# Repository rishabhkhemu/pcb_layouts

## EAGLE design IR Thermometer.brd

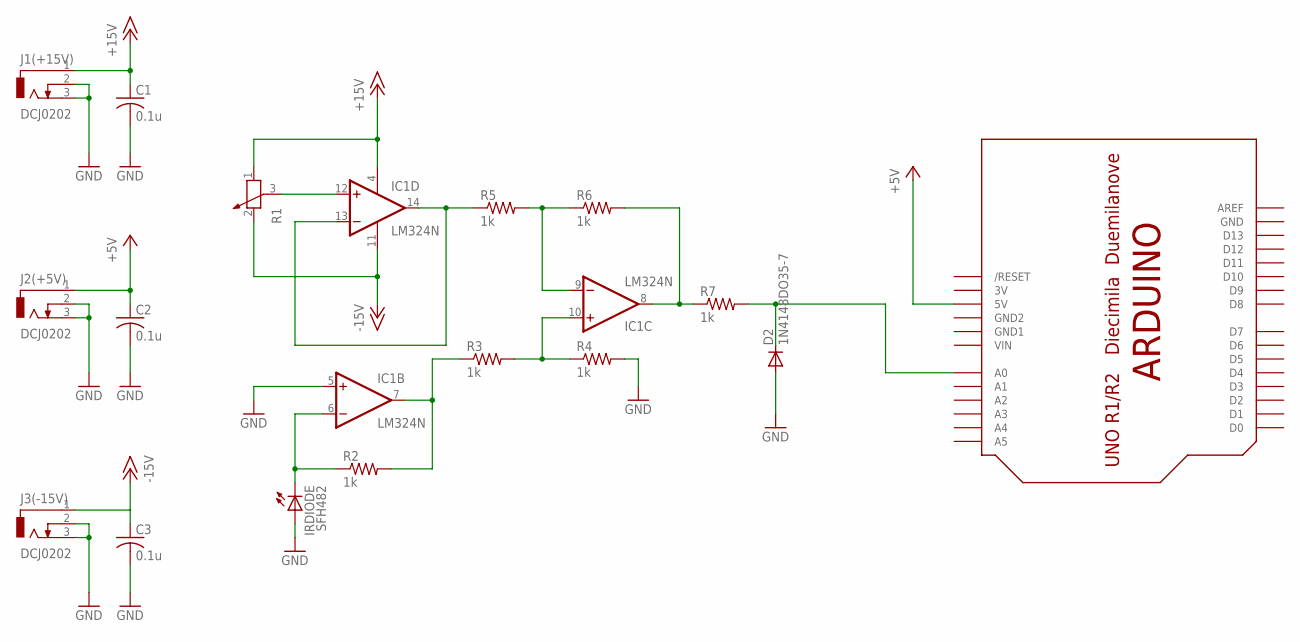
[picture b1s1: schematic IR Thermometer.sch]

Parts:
C1, C2, C3: 0.1u; C0805
D2: 1N4148DO35-7; DO35-7
IC1: LM324N; DIL14
IRDIODE: SFH482
J1(+15V), J2(+5V), J3(-15V): DCJ0202
R1: POTENTIOMETER_PT-10; PT-10
R2, R3, R4, R5, R6, R7: 1k; M0805
U$1: ARDUINOUNO; ARDUINO

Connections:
3V: U$1.3V
+5V: C2.1, J2(+5V).1, U$1.5V
+15V: C1.1, IC1.4 (V+), J1(+15V).1, R1.1
-15V: C3.1, IC1.11 (V-), J3(-15V).1, R1.2
GND: C1.2, C2.2, C3.2, D2.A, IC1.5 (+IN), IRDIODE.A, J1(+15V).2, J1(+15V).3, J2(+5V).2, J2(+5V).3, J3(-15V).2, J3(-15V).3, R4.2, U$1.GND; also elsewhere on the board
GND1: U$1.GND1
GND2: U$1.GND2
unnamed 7: IC1.6 (-IN), IRDIODE.K (C), R2.1; also elsewhere on the board
unnamed: IC1.7 (OUT), R2.2, R3.1
unnamed: IC1.10 (+IN), R3.2, R4.1
unnamed: IC1.9 (-IN), R5.2, R6.1
unnamed: IC1.13 (-IN), IC1.14 (OUT), R5.1
unnamed: IC1.8 (OUT), R6.2, R7.1
unnamed: D2.C, R7.2, U$1.A0
unnamed: IC1.12 (+IN), R1.3
VIN: U$1.VIN

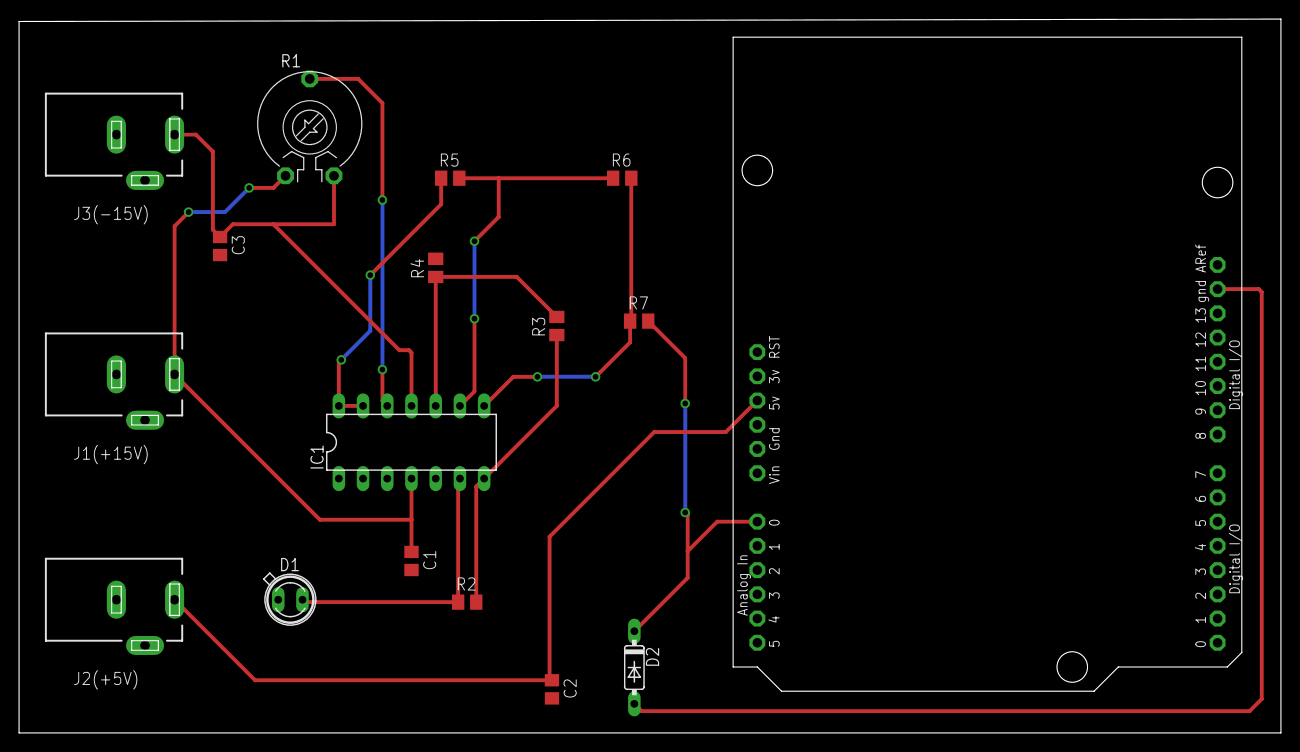
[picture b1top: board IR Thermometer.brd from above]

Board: 2 copper layers, 132.3 x 74.9 mm, 17 parts (0 on the bottom side), 12 nets.

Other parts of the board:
D1: SFH482

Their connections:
GND: D1.A; also elsewhere on the board
unnamed 7: D1.K; also elsewhere on the board
